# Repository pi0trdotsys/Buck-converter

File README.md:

# Buck-converter 🚧⚡

Projekt przetwornicy typu **Buck** (obniżającej napięcie) oparty na sterowniku IR2104 i tranzystorach mocy IGP20N65F5. Całość przygotowana w symulatorze **LTspice**, z możliwością implementacji w rzeczywistym układzie z mikrokontrolerem (np. ESP8266 do sterowania PWM).

## ⚙️ Cechy projektu

- Napięcie wejściowe: 24–100 V DC
- Napięcie wyjściowe: regulowane (zależnie od PWM)
- Topologia: półmostek H z przetwornicą typu Buck
- Sterowanie: sygnał PWM (np. z ESP8266)

## 🔌 Zastosowanie

Ten projekt może być użyty jako:

- regulator napięcia do zasilania urządzeń elektronicznych,
- baza do nauki projektowania przetwornic impulsowych,
- część większego systemu zasilania (np. z mikrokontrolerem IoT),
- zakres napięcia, w którym przetwornica działa stabilnie

## ⚡ Co zostanie zmierzone i przeanalizowane?

Jak zachowują się bramki tranzystorów?
Które elementy się nagrzewają?
Gdzie pojawiają się dudnienia?

## 📏 Pomiary

Pomiary wykonywane są oscyloskopem. Przy częstotliwościach **200 kHz i 300 kHz** pojawiają się
interesujące zjawiska przełączeniowe, które zostaną szczegółowo przeanalizowane.

## Dead time ⏱️

W mostku z dwoma tranzystorami (high-side + low-side) nigdy nie mogą być włączone jednocześnie — spowodowałoby to zwarcie zasilania (shoot-through).

Dead time to krótka przerwa między wyłączeniem jednego a włączeniem drugiego tranzystora, gdy oba są wyłączone jednocześnie. W IR2104 wynosi ~520 ns i jest generowany sprzętowo.

## Przebiegi do zbadania 📊

1. **HO** 🔵 — bramka Q1 (high-side). Przechodzi między 0 V a ~15 V (bootstrap). Pozwala sprawdzić czy IR2104 poprawnie steruje tranzystorem.

2. **LO** 🟢 — bramka Q2 (low-side), komplementarny do HO z widocznym dead time. Jeśli amplituda jest mniejsza niż HO, problem z zasilaniem części low-side drivera.

3. **V_SW** 🟠 — węzeł między drenem Q1 a źródłem Q2, czyli wyjście mocy przed cewką. Najważniejszy przebieg — prostokąt 0 V / V_in z ringiem na zboczach. Ujawnia pasożyty PCB, decyduje o EMI, pokazuje stan obu tranzystorów jednocześnie.

4. **I_L** 🟣 — prąd przez cewkę, mierzony przez rezystor bocznikowy (shunt) szeregowo z L1. Kształt trójkątny: rośnie gdy Q1 ON, opada gdy Q2 ON. Wartość średnia odpowiada V_out = V_in × D.

## EMI (Electromagnetic Interference) 📡

EMI to zakłócenia elektromagnetyczne — niecelowo emitowana energia, która interferuje z innymi urządzeniami lub samym układem. W przetwornicy głównym źródłem są strome zbocza V_SW, które powodują emisję w paśmie 20–100 MHz. Przy wyższych częstotliwościach przełączania (200–300 kHz) zakłócenia obejmują szersze widmo.

## 🔌 Schemat LTSpice

## 🖥️ Schemat Eagle

## 🗺️ Layout PCB

## 📊 Wyniki symulacji
Przebiegi V(vout) oraz I(L1) dla wypełnienia PWM D = 0.3 – 0.7:
.png)

## 📋 Ocena z projektu

Projekt składa się z dwóch części, do których przygotowujemy osobne raporty:
- **a)** Symulacja anteny (MATLAB)
- **b)** Płytka PCB i pomiary

## 📝 Kolokwium

- Odbywa się na **drugich zajęciach od końca**
- Dwie części (odpowiadające częściom projektu)
- Ocena na podstawie **sumy punktów** z obu kolokwiów — każde z osobna nie musi być zaliczone

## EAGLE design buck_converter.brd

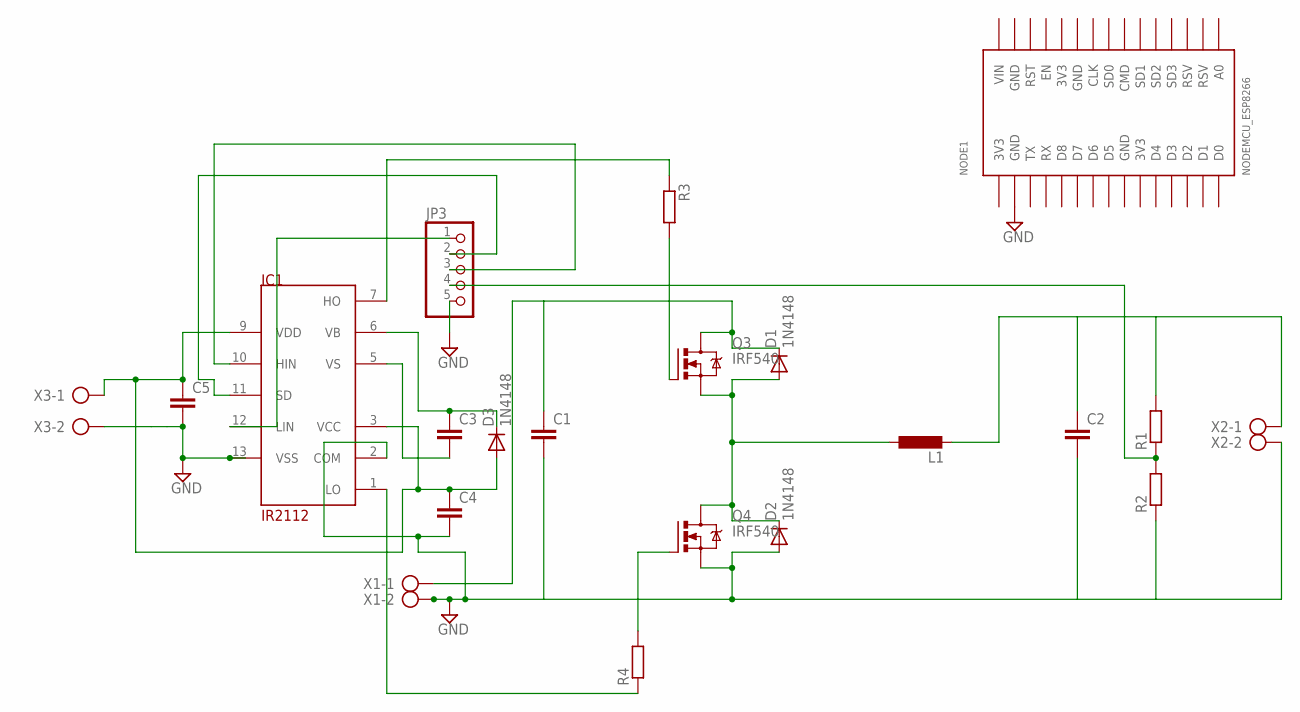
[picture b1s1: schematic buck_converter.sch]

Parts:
C1, C2: C-EU025-060X050; C025-060X050
C3, C4, C5: C-EU025-025X050; C025-025X050
D1, D2, D3: 1N4148; DO35-10
IC1: IR2112; DIL14
JP3: PINHD-1X5; 1X05
L1: L-EU0207/10; 0207/10
NODE1: NODEMCU_ESP8266
Q3, Q4: IRF540; TO220BV
R1, R2, R3, R4: R-EU_0207/12; 0207/12
X1, X2, X3: AK500/2-H

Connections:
3V3: NODE1.3V3@1 (3V3), NODE1.3V3@2 (3V3), NODE1.3V3@3 (3V3)
unnamed: IC1.10 (HIN), JP3.3
unnamed: D1.A, D2.C, L1.1, Q3.S, Q4.D
unnamed: C1.1, D1.C, Q3.D, X1.1
unnamed: C2.1, L1.2, R1.2, X2.1
unnamed: JP3.4, R1.1, R2.2
unnamed: IC1.11 (SD), JP3.2
unnamed: Q3.G, R3.2
unnamed: IC1.7 (HO), R3.1
unnamed: IC1.1 (LO), R4.1
unnamed: IC1.12 (LIN), JP3.1
unnamed: Q4.G, R4.2
SIGNAL: C1.2, C2.2, C4.2, C5.2, D2.A, IC1.2 (COM), IC1.13 (VSS), JP3.5, NODE1.GND@1 (GND), NODE1.GND@2 (GND), NODE1.GND@3 (GND), NODE1.GND@4 (GND), Q4.S, R2.1, X1.2, X2.2, X3.2
VB: C3.1, D3.C, IC1.6 (VB)
VCC: C4.1, C5.1, D3.A, IC1.3 (VCC), IC1.9 (VDD), X3.1
VIN: NODE1.VIN
VS: C3.2, IC1.5 (VS)

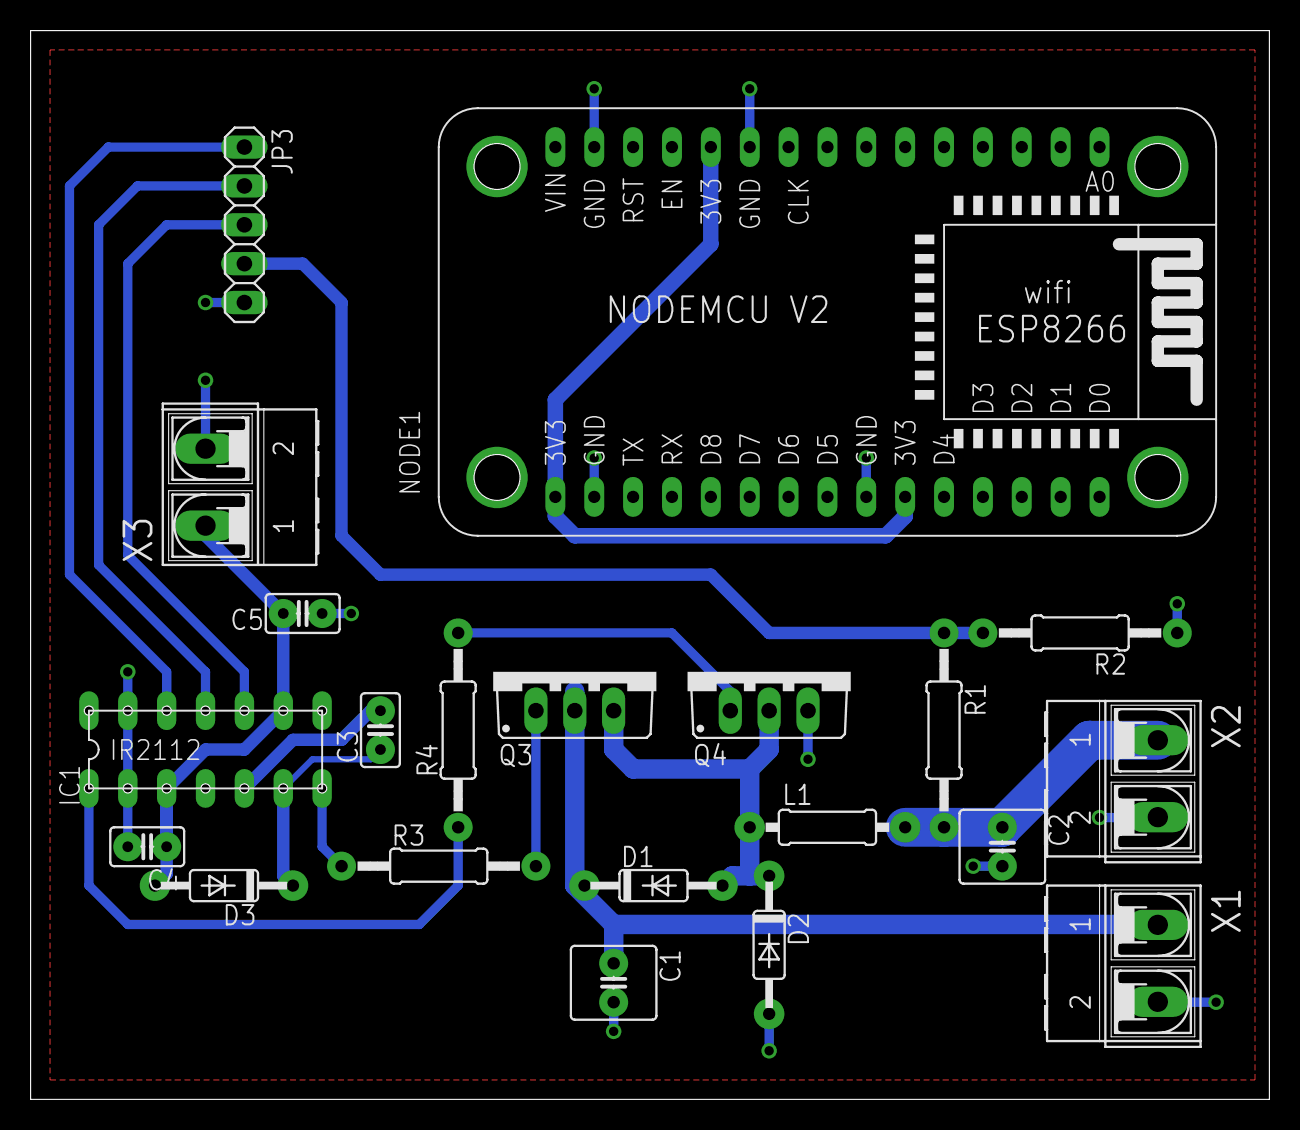
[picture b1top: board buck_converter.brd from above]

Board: 2 copper layers, 81.0 x 69.8 mm, 21 parts (0 on the bottom side), 16 nets.

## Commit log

2025-07-24 introduce the whole project
2025-07-24 updated README.md 2
2026-03-11 Classes 11.03
    ### Opis zajęć
    Repozytorium zawiera skrypt przygotowany w środowisku **MATLAB** z wykorzystaniem pakietu **MATLAB Antenna Toolbox**, którego celem jest zaprojektowanie oraz analiza anteny typu **Inverted-F Antenna*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
    W pierwszym etapie generowany jest model anteny oraz wizualizacja jej geometrii. Następnie wykonywana jest analiza parametrów rozproszenia **S-parameters** w zakresie częstotliwości od **2 GHz do 3 G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
    Kolejny etap obejmuje budowę modelu struktury **PCB stack**, w której definiowane są właściwości materiałow
2026-03-25 added notes from classes 25.03
2026-03-25 added .gitignore
2026-03-26 improved Fcoplanar antenna Matlab script
2026-03-26 added series resistance
2026-05-06 improved LTSpice & added .sch
2026-05-06 Enhance README with schematics and simulation results
    Added LTSpice, Eagle schematics, PCB layout, and simulation results sections to README.
2026-05-14 v1 of the report
